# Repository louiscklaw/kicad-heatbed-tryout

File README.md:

# README

### Design criteria (To be verified)
  - 130mm(W) x 130mm(H)
  - double sided PCB
  - M3 mounting
  - LED indication/operation
  - 12V version only, around 100W at full load (25 Deg, current@8.7A)
  - Designed top temperature running at 150 Deg

### references
https://github.com/fmalpartida/heatbed-mini
https://github.com/prusa3d/Heatbed_MK52_magnetic

https://www.elektrisola.com/conductor-materials/copper.html

https://www.elektrisola.com/fileadmin/webdata/english/Downloads/ELEKTRISOLA_Datasheet_Cu.pdf

https://github.com/mtl/svg2mod

https://github.com/dvc94ch/pykicad

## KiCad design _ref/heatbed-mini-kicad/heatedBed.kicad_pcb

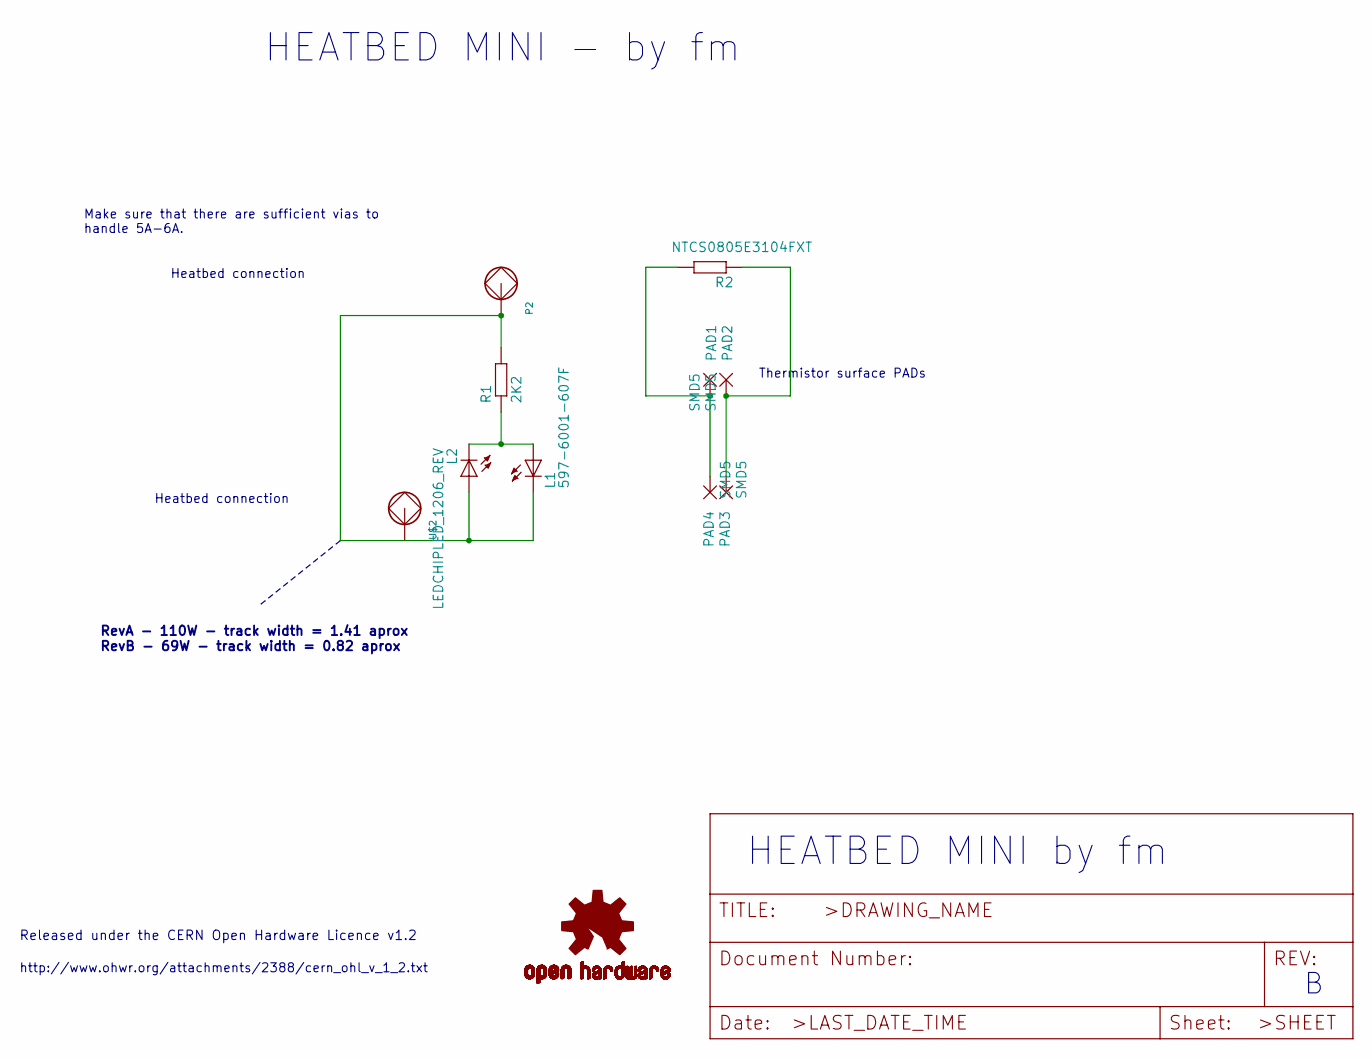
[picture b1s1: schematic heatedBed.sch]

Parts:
L1: 597-6001-607F; CHIPLED_1206_REVERSE
L2: LEDCHIPLED_1206_REV; CHIPLED_1206_REVERSE
P2: LONG_PAD
PAD1, PAD2, PAD3, PAD4: SMD5; SMD2,54-5,08
R1: 2K2; R0805
R2: NTCS0805E3104FXT; R0805
U$2: LONG_PAD
U$5: SPARKFUN_OSHW-LOGOL; SPARKFUN_OSHW-LOGO-L

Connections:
unnamed: L1.A, L2.C, R1.1
unnamed: L1.C, L2.A, P2.P$1, P2.P$2, P2.P$3, R1.2, U$2.P$1, U$2.P$2, U$2.P$3
unnamed: PAD1.1, PAD4.1, R2.2
unnamed: PAD2.1, PAD3.1, R2.1

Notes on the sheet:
Released under the CERN Open Hardware Licence v1.2
HEATBED MINI by fm
Heatbed connection
Make sure that there are sufficient vias to handle 5A-6A.
Thermistor surface PADs
http://www.ohwr.org/attachments/2388/cern_ohl_v_1_2.txt
HEATBED MINI - by fm
RevA - 110W - track width = 1.41 aprox RevB - 69W - track width = 0.82 aprox

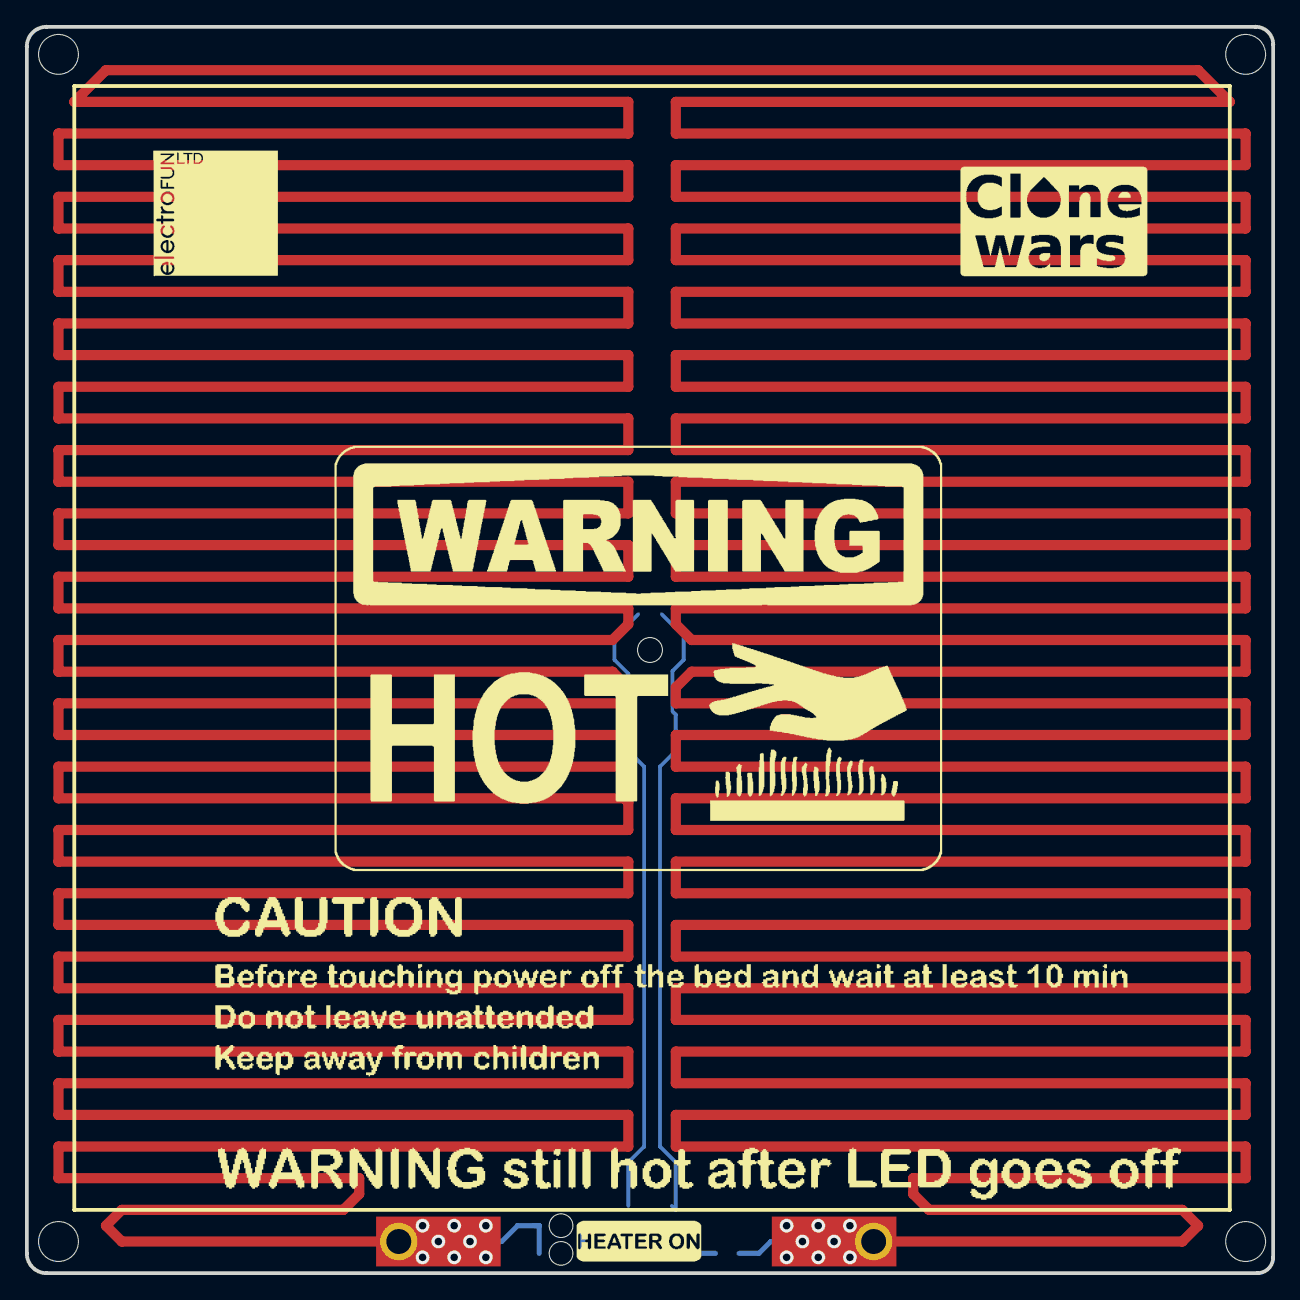
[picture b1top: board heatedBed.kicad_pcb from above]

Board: 2 copper layers, 100.0 x 100.0 mm, 26 parts (0 on the bottom side), 4 nets.

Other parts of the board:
@HOLE0, @HOLE1, @HOLE2, @HOLE3, @HOLE4: (no value)
U$1: CAUTION
U$3, U$7: CLONE_WARS
U$4: CERN_OHL
U$6: ELECTROFUN_STRIP
U$8: BOARD_REF
U$9: HEATERON
U$10: WARNING_HOT
U$11: ELECTROFUN_20X20
U$12: ELECTROFUN_10X10

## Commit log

2020-05-09 init working commit,
2020-05-09 working with parameters,
2020-05-09 add calculation sheet,
2020-05-09 update print done,
2020-05-09 add length calculation,
2020-05-09 ci: init travis helloworld,
2020-05-09 update travis.yml and test,
2020-05-09 docs: update readme and references,
2020-05-09 update for tidy up scripts,
2020-05-09 update and test travis,
2020-05-11 init gitignore,
2020-05-11 in the middle,
2020-05-11 add gitignore,
2020-05-11 convert eagle to kicad,
2020-05-11 init commit,
2020-05-11 fix for test_heatbed.sh script,
2020-05-11 ignore ods temp file,
2020-05-11 print power rating on the board,
2020-05-11 update to enlarge pad,
2020-05-11 add thru hold on terminal 1 and 2,
2020-05-11 init commit for front led,
2020-05-11 update README,
2020-05-11 update for pre-final version,
2020-05-11 update for screen capture,
2020-05-11 update power calculation,
2020-05-11 add prusa heatbed github link,
2020-05-15 ci: update travis credentials.yml,
2020-09-10 update,
2020-09-18 test and update,
2020-09-18 init test_kicad_template_helloworld,
2020-09-18 update and test,
2020-09-18 init heatbed helloworld,
2020-09-18 update for test_check_y_inside,
2020-10-27 Bump cryptography from 2.9.2 to 3.2 in /github-build-merger
    Bumps [cryptography](https://github.com/pyca/cryptography) from 2.9.2 to 3.2.
    - [Release notes](https://github.com/pyca/cryptography/releases)
    - [Changelog](https://github.com/pyca/cryptography/blob/master/CHANGELOG.rst)
    - [Commits](https://github.com/pyca/cryptography/compare/2.9.2...3.2)
2021-02-26 Bump aiohttp from 3.6.2 to 3.7.4 in /github-build-merger
    Bumps [aiohttp](https://github.com/aio-libs/aiohttp) from 3.6.2 to 3.7.4.
    - [Release notes](https://github.com/aio-libs/aiohttp/releases)
    - [Changelog](https://github.com/aio-libs/aiohttp/blob/master/CHANGES.rst)
    - [Commits](https://github.com/aio-libs/aiohttp/compare/v3.6.2...v3.7.4)
2022-03-29 Bump paramiko from 2.7.1 to 2.10.1 in /github-build-merger
    Bumps [paramiko](https://github.com/paramiko/paramiko) from 2.7.1 to 2.10.1.
    - [Release notes](https://github.com/paramiko/paramiko/releases)
    - [Changelog](https://github.com/paramiko/paramiko/blob/main/NEWS)
    - [Commits](https://github.com/paramiko/paramiko/compare/2.7.1...2.10.1)
    ---
    updated-dependencies:
